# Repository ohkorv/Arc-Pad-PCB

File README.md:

Disclaimer! Currently non functional, pins for the oled are configured wrong. Possible to fix in software

# Arc Pad

# Only 28 dollars for all parts.
This is the cost for all part for one Arc Pad. Of course price will be different at times. For me the price included one pcb, one 0.96 Oled, TFT SPI 1.8 INCH, 9 XM SWITCHES, 9 KEYCAPS , TWO 6MM TACTILE BUTTONS AND ONE RASPBERRY PI PICO 2 W.

# Powered by a Raspberry Pi Pico 2 W.

It uses a Raspberry Pi Pico 2 W for a powerful and reliable use. Feel free to change the microcontroller to you needs.

# Open source software under development.

I am working on the software for this macropad.

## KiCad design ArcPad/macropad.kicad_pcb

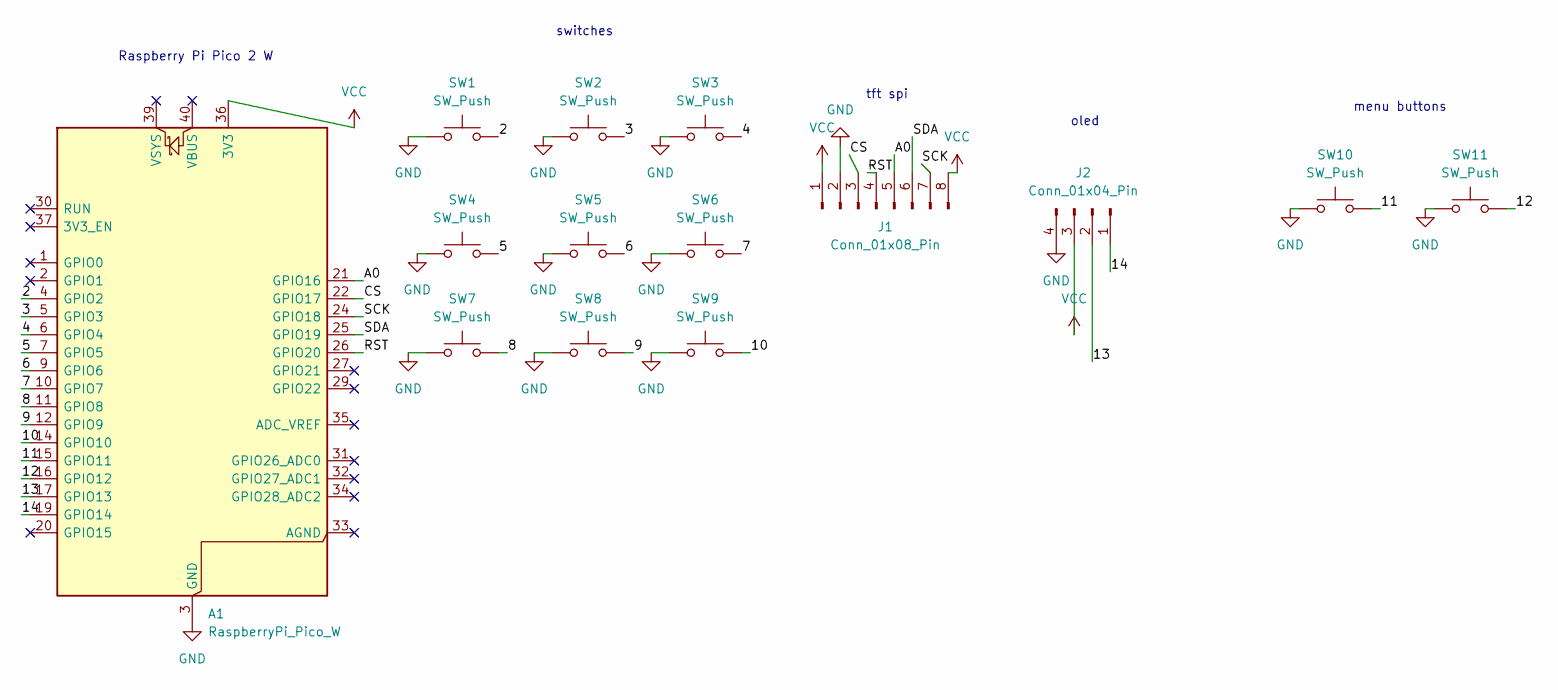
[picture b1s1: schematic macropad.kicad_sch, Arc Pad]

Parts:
A1: RaspberryPi_Pico_W; RaspberryPi_Pico_Common_THT
J1: Conn_01x08_Pin; PinSocket_1x08_P2.54mm_Vertical
J2: Conn_01x04_Pin; PinSocket_1x04_P2.54mm_Vertical
SW1, SW2, SW3, SW4, SW5, SW6, SW7, SW8, SW9: SW_Push; SW_Cherry_MX_1.00u_PCB
SW10, SW11: SW_Push; SW_PUSH_6mm_H4.3mm

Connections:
/2: A1.4 (GPIO2), SW1.2
/3: A1.5 (GPIO3), SW2.2
/4: A1.6 (GPIO4), SW3.2
/5: A1.7 (GPIO5), SW4.2
/6: A1.9 (GPIO6), SW5.2
/7: A1.10 (GPIO7), SW6.2
/8: A1.11 (GPIO8), SW7.2
/9: A1.12 (GPIO9), SW8.2
/10: A1.14 (GPIO10), SW9.2
/11: A1.15 (GPIO11), SW10.2
/12: A1.16 (GPIO12), SW11.2
/13: A1.17 (GPIO13), J2.2
/14: A1.19 (GPIO14), J2.1
/A0: A1.21 (GPIO16), J1.5
/CS: A1.22 (GPIO17), J1.3
/RST: A1.26 (GPIO20), J1.4
/SCK: A1.24 (GPIO18), J1.7
/SDA: A1.25 (GPIO19), J1.6
GND: A1.3 (GND), A1.8 (GND), A1.13 (GND), A1.18 (GND), A1.23 (GND), A1.28 (GND), A1.38 (GND), J1.2, J2.4, SW1.1, SW2.1, SW3.1, SW4.1, SW5.1, SW6.1, SW7.1, SW8.1, SW9.1, SW10.1, SW11.1
VCC: A1.36 (3V3), J1.1, J1.8, J2.3

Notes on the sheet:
Raspberry Pi Pico 2 W
menu buttons
oled
switches
tft spi

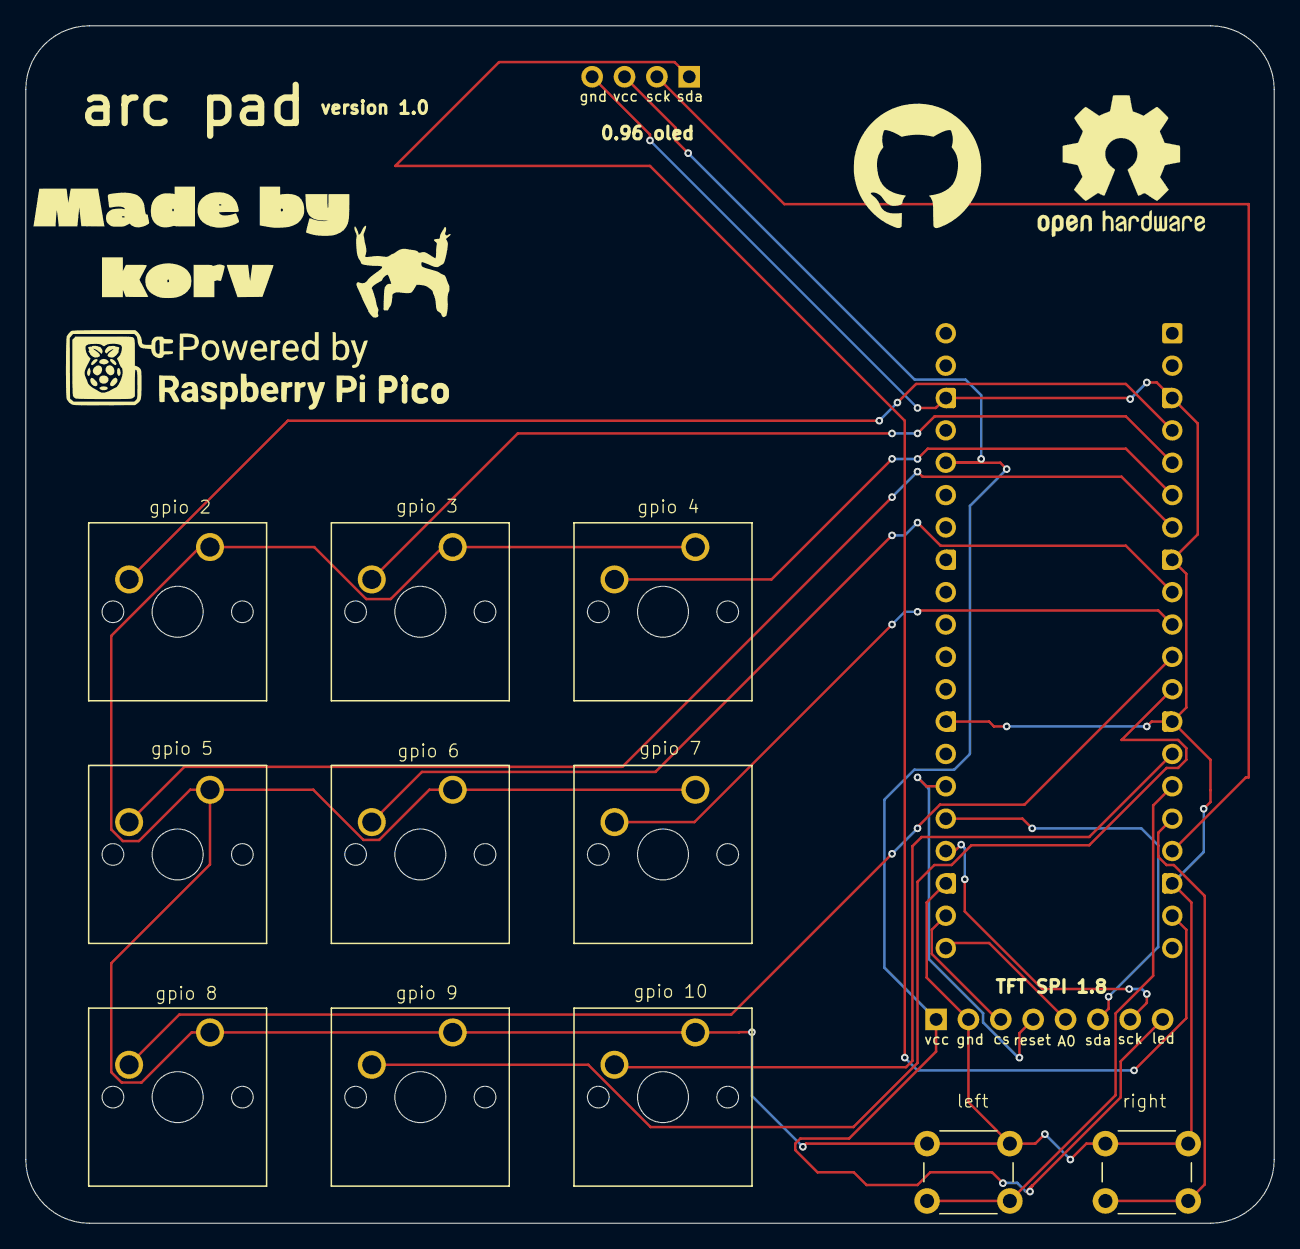
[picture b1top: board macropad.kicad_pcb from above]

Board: 2 copper layers, 98.0 x 94.0 mm, 14 parts (1 on the bottom side), 20 nets.

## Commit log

2026-05-17 Updated Read Me
2026-05-17 Updated Rendering Files
2026-05-17 small schematic change
2026-05-18 basic changes
2026-05-31 Add disclaimer about non-functional OLED configuration
    Added a disclaimer about the non-functional state of the project due to incorrect OLED pin configuration.
